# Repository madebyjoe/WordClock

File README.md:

# PCB, and PCB related items

Contains

* Schematic
* Board Layout
* BOM
* Gerber Files

Please see https://github.com/madebyjoe/WordClockController for the electronics setup.

Images of the project [can be viewed here](https://photos.app.goo.gl/oPhYEB3sT6SlBXRt1).

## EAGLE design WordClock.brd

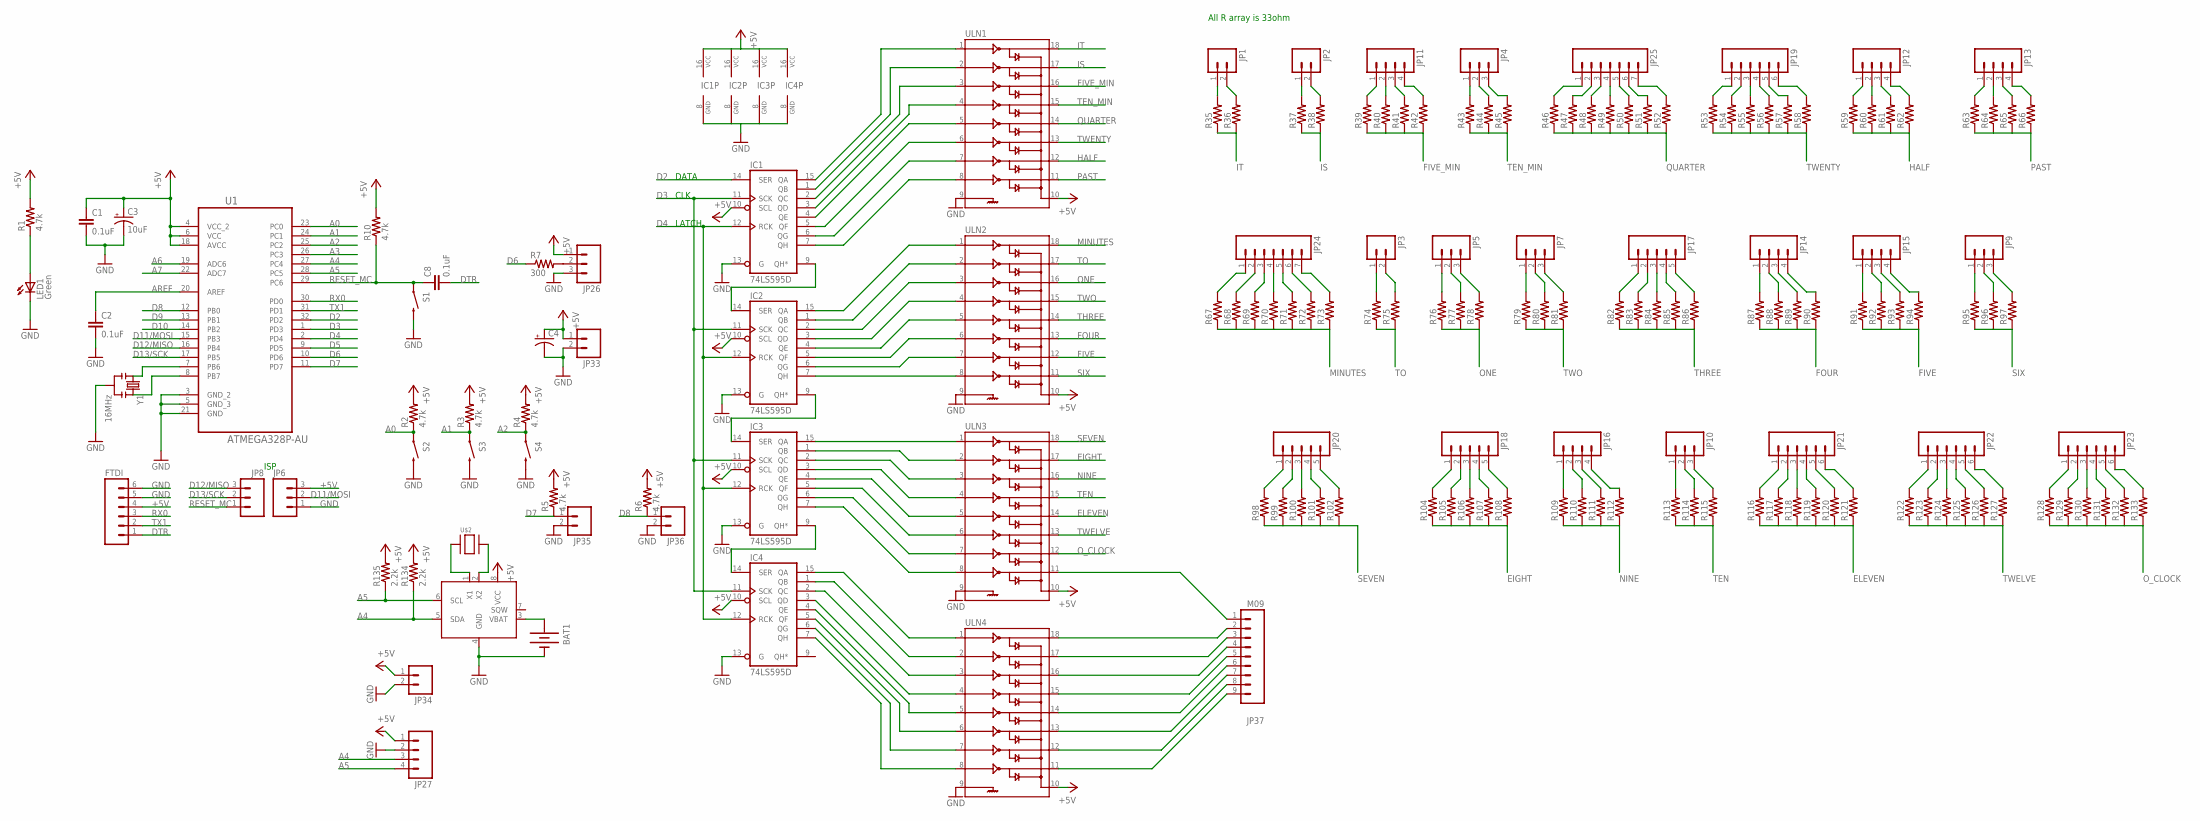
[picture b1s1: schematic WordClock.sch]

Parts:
BAT1: BATTERY12MM; BATTCON_12MM
C1, C2, C8: 0.1uF; 0402-CAP
C3: 10uF; EIA3216
C4: CPOL-USF; PANASONIC_F
FTDI: M06SIP; 1X06
IC1, IC2, IC3, IC4: 74LS595D; SO16
JP1, JP2, JP3, JP33, JP34, JP35, JP36: M02PTH; 1X02
JP4, JP5, JP6, JP7, JP8, JP9, JP10, JP26: M03PTH; 1X03
JP11, JP12, JP13, JP14, JP15, JP16, JP27: M04PTH; 1X04
JP17, JP18, JP20: M05PTH; 1X05
JP19, JP21, JP22, JP23: M06SIP; 1X06
JP24, JP25: M07; 1X07
JP37: M09; 1X09
LED1: Green; LED-0603
R1, R10: 4.7k; R0603
R2, R3, R4, R5, R6: 4.7k; 0603-RES
R7: 300; 0603-RES
R35, R36, R37, R38, R39, R40, R41, R42, R43, R44, R45, R46, R47, R48, R49, R50, R51, R52, R53, R54, R55, R56, R57, R58, R59, R60, R61, R62, R63, R64, R65, R66, R67, R68, R69, R70, R71, R72, R73, R74, R75, R76, R77, R78, R79, R80, R81, R82, R83, R84, R85, R86, R87, R88, R89, R90, R91, R92, R93, R94, R95, R96, R97, R98, R99, R100, R101, R102, R104, R105, R106, R107, R108, R109, R110, R111, R112, R113, R114, R115, R116, R117, R118, R119, R120, R121, R122, R123, R124, R125, R126, R127, R128, R129, R130, R131, R132, R133: RESISTOR0603-RES; 0603-RES
R134, R135: 2.2k; 0603-RES
S1, S2, S3, S4: SWITCH-MOMENTARY-2; TACTILE_SWITCH_TALL
U1: ATMEGA328P-AU; QFP80P900X900X120-32N
U$1: DS1307; 8-SOIC
U$2: CRYSTAL-32.768K; 4-SOJ
ULN1, ULN2, ULN3, ULN4: ULN2803SOICW; SO18L
Y1: 16MHz; RESONATOR-SMD

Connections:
+5V: C1.1, C3.A (+), C4.+, FTDI.4, IC1.10 (SCL), IC1.16 (VCC), IC2.10 (SCL), IC2.16 (VCC), IC3.10 (SCL), IC3.16 (VCC), IC4.10 (SCL), IC4.16 (VCC), JP6.3, JP26.1, JP27.1, JP33.1, JP34.1, R1.2, R2.2, R3.2, R4.2, R5.2, R6.2, R10.2, R134.2, R135.2, U1.4 (VCC_2), U1.6 (VCC), U1.18 (AVCC), U$1.8 (VCC), ULN1.10, ULN2.10, ULN3.10, ULN4.10
A0: R2.1, S2.A2 (1), U1.23 (PC0)
A1: R3.1, S3.A2 (1), U1.24 (PC1)
A2: R4.1, S4.A2 (1), U1.25 (PC2)
A3: U1.26 (PC3)
A4: JP27.3, R134.1, U1.27 (PC4), U$1.5 (SDA)
A5: JP27.4, R135.1, U1.28 (PC5), U$1.6 (SCL)
A6: U1.19 (ADC6)
A7: U1.22 (ADC7)
AREF: C2.1, U1.20 (AREF)
D2: IC1.14 (SER), U1.32 (PD2)
D3: IC1.11 (SCK), IC2.11 (SCK), IC3.11 (SCK), IC4.11 (SCK), U1.1 (PD3)
D4: IC1.12 (RCK), IC2.12 (RCK), IC3.12 (RCK), IC4.12 (RCK), U1.2 (PD4)
D5: U1.9 (PD5)
D6: R7.1, U1.10 (PD6)
D7: JP35.1, R5.1, U1.11 (PD7)
D8: JP36.1, R6.1, U1.12 (PB0)
D9: U1.13 (PB1)
D10: U1.14 (PB2)
D11/MOSI: JP6.2, U1.15 (PB3)
D12/MISO: JP8.3, U1.16 (PB4)
D13/SCK: JP8.2, U1.17 (PB5)
DTR: C8.2, FTDI.1
EIGHT: R104.1, R105.1, R106.1, R107.1, R108.1, ULN3.17
ELEVEN: R116.1, R117.1, R118.1, R119.1, R120.1, R121.1, ULN3.14
FIVE: R91.1, R92.1, R93.1, R94.1, ULN2.12
FIVE_MIN: R39.1, R40.1, R41.1, R42.1, ULN1.16
FOUR: R87.1, R88.1, R89.1, R90.1, ULN2.13
GND: BAT1.GND (-), C1.2, C2.2, C3.C (-), C4.-, FTDI.5, FTDI.6, IC1.8 (GND), IC1.13 (G), IC2.8 (GND), IC2.13 (G), IC3.8 (GND), IC3.13 (G), IC4.8 (GND), IC4.13 (G), JP6.1, JP26.3, JP27.2, JP33.2, JP34.2, JP35.2, JP36.2, LED1.C, S1.B2 (2), S2.B2 (2), S3.B2 (2), S4.B2 (2), U1.3 (GND_2), U1.5 (GND_3), U1.21 (GND), U$1.4 (GND), ULN1.9, ULN2.9, ULN3.9, ULN4.9, Y1.2
HALF: R59.1, R60.1, R61.1, R62.1, ULN1.12
IS: R37.1, R38.1, ULN1.17
IT: R35.1, R36.1, ULN1.18
MINUTES: R67.1, R68.1, R69.1, R70.1, R71.1, R72.1, R73.1, ULN2.18
unnamed: U1.7 (PB6), Y1.1
unnamed: LED1.A, R1.1
unnamed: U1.8 (PB7), Y1.3
unnamed: BAT1.PWR@1 (+), U$1.3 (VBAT)
unnamed: IC1.9 (QH*), IC2.14 (SER)
unnamed: IC2.9 (QH*), IC3.14 (SER)
unnamed: IC3.9 (QH*), IC4.14 (SER)
unnamed: U$1.2 (X2), U$2.P$4
unnamed: U$1.1 (X1), U$2.P$1
unnamed: JP37.1, ULN3.11
unnamed: JP37.2, ULN4.18
unnamed: JP37.3, ULN4.17
unnamed: JP37.4, ULN4.16
unnamed: JP37.5, ULN4.15
unnamed: JP37.6, ULN4.14
unnamed: JP37.7, ULN4.13
unnamed: JP37.8, ULN4.12
unnamed: JP37.9, ULN4.11
unnamed: JP26.2, R7.2
unnamed: IC2.7 (QH), ULN2.8
unnamed: IC2.6 (QG), ULN2.7
unnamed: IC2.5 (QF), ULN2.6
unnamed: IC2.4 (QE), ULN2.5
unnamed: IC2.3 (QD), ULN2.4
unnamed: IC2.2 (QC), ULN2.3
unnamed: IC2.1 (QB), ULN2.2
unnamed: IC2.15 (QA), ULN2.1
unnamed: IC1.7 (QH), ULN1.8
unnamed: IC1.6 (QG), ULN1.7
unnamed: IC1.5 (QF), ULN1.6
unnamed: IC1.4 (QE), ULN1.5
unnamed: IC3.15 (QA), ULN3.1
unnamed: IC3.1 (QB), ULN3.2
unnamed: IC3.2 (QC), ULN3.3
unnamed: IC3.3 (QD), ULN3.4
unnamed: IC3.4 (QE), ULN3.5
unnamed: IC3.5 (QF), ULN3.6
unnamed: IC3.6 (QG), ULN3.7
unnamed: IC3.7 (QH), ULN3.8
unnamed: IC1.3 (QD), ULN1.4
unnamed: IC1.2 (QC), ULN1.3
unnamed: IC1.1 (QB), ULN1.2
unnamed: IC1.15 (QA), ULN1.1
unnamed: IC4.15 (QA), ULN4.1
unnamed: IC4.1 (QB), ULN4.2
unnamed: IC4.2 (QC), ULN4.3
unnamed: IC4.3 (QD), ULN4.4
unnamed: IC4.4 (QE), ULN4.5
unnamed: IC4.5 (QF), ULN4.6
unnamed: IC4.6 (QG), ULN4.7
unnamed: IC4.7 (QH), ULN4.8
unnamed: JP1.1, R35.2
unnamed: JP1.2, R36.2
unnamed: JP2.1, R37.2
unnamed: JP2.2, R38.2
unnamed: JP3.1, R74.2
unnamed: JP3.2, R75.2
unnamed: JP4.1, R43.2
unnamed: JP4.2, R44.2
unnamed: JP4.3, R45.2
unnamed: JP5.1, R76.2
unnamed: JP5.2, R77.2
unnamed: JP5.3, R78.2
unnamed: JP7.1, R79.2
unnamed: JP7.2, R80.2
unnamed: JP7.3, R81.2
unnamed: JP14.1, R87.2
unnamed: JP14.2, R88.2
unnamed: JP14.3, R89.2
unnamed: JP14.4, R90.2
unnamed: JP15.1, R91.2
unnamed: JP15.2, R92.2
unnamed: JP15.3, R93.2
unnamed: JP15.4, R94.2
unnamed: JP9.1, R95.2
unnamed: JP9.2, R96.2
unnamed: JP9.3, R97.2
unnamed: JP16.1, R109.2
unnamed: JP16.2, R110.2
unnamed: JP16.3, R111.2
unnamed: JP16.4, R112.2
unnamed: JP10.1, R113.2
unnamed: JP10.2, R114.2
unnamed: JP10.3, R115.2
unnamed: JP25.1, R46.2
unnamed: JP25.2, R47.2
unnamed: JP25.3, R48.2
unnamed: JP25.4, R49.2
unnamed: JP25.5, R50.2
unnamed: JP25.6, R51.2
unnamed: JP25.7, R52.2
unnamed: JP19.1, R53.2
unnamed: JP19.2, R54.2
unnamed: JP19.3, R55.2
unnamed: JP19.4, R56.2
unnamed: JP19.5, R57.2
unnamed: JP19.6, R58.2
unnamed: JP12.1, R59.2
unnamed: JP12.2, R60.2
unnamed: JP12.3, R61.2
unnamed: JP12.4, R62.2
unnamed: JP13.1, R63.2
unnamed: JP13.2, R64.2
unnamed: JP13.3, R65.2
unnamed: JP13.4, R66.2
unnamed: JP24.1, R67.2
unnamed: JP24.2, R68.2
unnamed: JP24.3, R69.2
unnamed: JP24.4, R70.2
unnamed: JP24.5, R71.2
unnamed: JP24.6, R72.2
unnamed: JP24.7, R73.2
unnamed: JP17.1, R82.2
unnamed: JP17.2, R83.2
unnamed: JP17.3, R84.2
unnamed: JP17.4, R85.2
unnamed: JP17.5, R86.2
unnamed: JP20.1, R98.2
unnamed: JP20.2, R99.2
unnamed: JP20.3, R100.2
unnamed: JP20.4, R101.2
unnamed: JP20.5, R102.2
unnamed: JP18.1, R104.2
unnamed: JP18.2, R105.2
unnamed: JP18.3, R106.2
unnamed: JP18.4, R107.2
unnamed: JP18.5, R108.2
unnamed: JP21.1, R116.2
unnamed: JP21.2, R117.2
unnamed: JP21.3, R118.2
unnamed: JP21.4, R119.2
unnamed: JP21.5, R120.2
unnamed: JP21.6, R121.2
unnamed: JP22.1, R122.2
unnamed: JP22.2, R123.2
unnamed: JP22.3, R124.2
unnamed: JP22.4, R125.2
unnamed: JP22.5, R126.2
unnamed: JP22.6, R127.2
unnamed: JP23.1, R128.2
unnamed: JP23.2, R129.2
unnamed: JP23.3, R130.2
unnamed: JP23.4, R131.2
unnamed: JP23.5, R132.2
unnamed: JP23.6, R133.2
unnamed: JP11.1, R39.2
unnamed: JP11.2, R40.2
unnamed: JP11.3, R41.2
unnamed: JP11.4, R42.2
NINE: R109.1, R110.1, R111.1, R112.1, ULN3.16
ONE: R76.1, R77.1, R78.1, ULN2.16
O_CLOCK: R128.1, R129.1, R130.1, R131.1, R132.1, R133.1, ULN3.12
PAST: R63.1, R64.1, R65.1, R66.1, ULN1.11
QUARTER: R46.1, R47.1, R48.1, R49.1, R50.1, R51.1, R52.1, ULN1.14
RESET_MC: C8.1, JP8.1, R10.1, S1.A2 (1), U1.29 (PC6)
RX0: FTDI.3, U1.30 (PD0)
SEVEN: R98.1, R99.1, R100.1, R101.1, R102.1, ULN3.18
SIX: R95.1, R96.1, R97.1, ULN2.11
TEN: R113.1, R114.1, R115.1, ULN3.15
TEN_MIN: R43.1, R44.1, R45.1, ULN1.15
THREE: R82.1, R83.1, R84.1, R85.1, R86.1, ULN2.14
TO: R74.1, R75.1, ULN2.17
TWELVE: R122.1, R123.1, R124.1, R125.1, R126.1, R127.1, ULN3.13
TWENTY: R53.1, R54.1, R55.1, R56.1, R57.1, R58.1, ULN1.13
TWO: R79.1, R80.1, R81.1, ULN2.15
TX1: FTDI.2, U1.31 (PD1)

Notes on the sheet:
ISP
DATA
CLK
LATCH
All R array is 33ohm

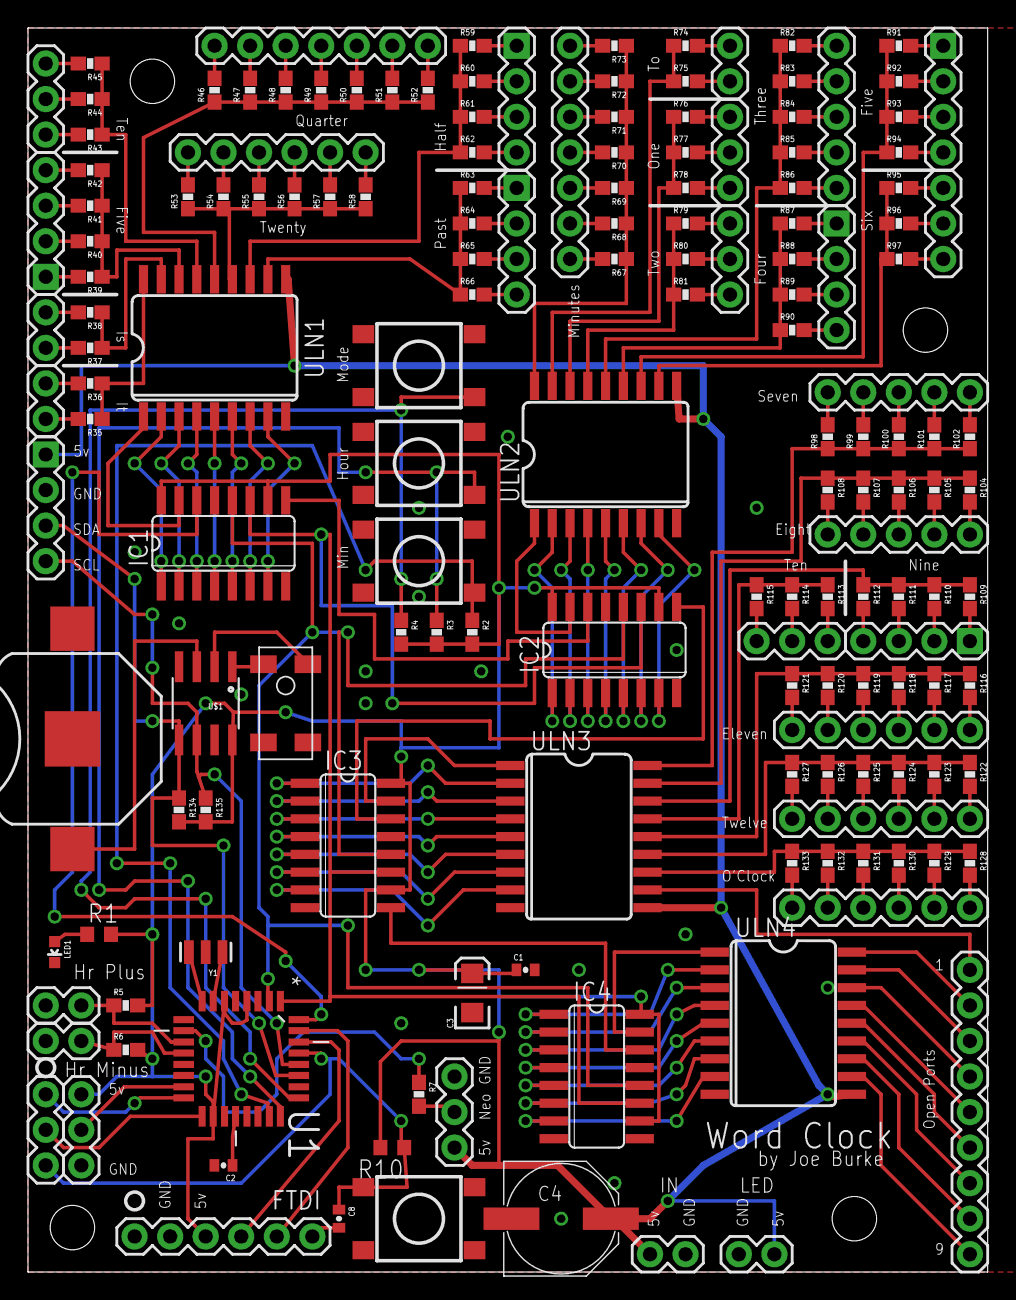
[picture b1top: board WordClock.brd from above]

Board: 2 copper layers, 68.6 x 88.9 mm, 164 parts (0 on the bottom side), 193 nets.

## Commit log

2018-02-09 Initial Commit. Finished PCB with gerber files.
2018-02-09 Created license file
2018-02-09 2016 copywrite
2018-02-09 updated readme.

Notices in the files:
parts and their libraries:
SparkFun-LED: Licensing: CC v3.0 Share-Alike You are welcome to use this library for commercial purposes.
